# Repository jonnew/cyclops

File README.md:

## Cyclops LED Driver
Precision, wide-bandwidth current source with optional optical feedback mode
for driving high-power LEDs and laser diodes. Good for sneaking optogenetic
stimuli between fast things (e.g. galvo flyback on a 2P system). Good for
_really_ controlling the amount of light you deliver during 1P imaging or
optogenetic stimulation.

If you have questions or comments, please come talk on the [open-ephys discord server](https://discord.gg/H2pH4Cp8xb) 
in the #stimulation channel.

### Features
- Ultra-precise
- High power
- Up to 1.5A per LED
- Wide bandwidth
    - \~2.5 MHz -3 dB bandwidth
    - Maximum 100 ns 1.0A rise and fall times
- Current and optical feedback modes
- Built-in waveform generation
- Over-current protection
- Modular
    - Arduino compatible: internal waveform generation
    - Also, accepts external analog, gate, or trigger inputs

### Stimulus generation options
- External stimulus sequencer
- External digital trigger
    - TTL logic level
- External analog waveform generator
    - 0-5V analog signals
- Internal 12-bit DAC
    - Synchronized across up to 4 drivers
    - Arduino library
    - Programmable triggering logic
    - Respond to USB input

### Buying one
You can purchase a fully assembled cyclops driver from the [open-ephys
store](https://open-ephys.org/cyclops-led-driver). All profits go towards continued
operation of open-ephys.

### Documentation
Documentation and usage information are here: [MANUAL.pdf](./MANUAL.pdf). If you
have questions concerning usage, performance, etc., please direct them toward
the [Open Ephys forum](https://groups.google.com/forum/#!forum/open-ephys).

### Hardware Licensing
Copyright Jonathan P. Newman 2020.

This work is licensed under CC BY-NC-SA 4.0. To view a copy of this license,
visit https://creativecommons.org/licenses/by-nc-sa/4.0

__Note__: This license applies to hardware designs and documentation which reside
in the 'device', 'experimental', 'resources' folders of this repository along
with information in 'MANUAL.md' and 'MANUAL.pdf'

### Software Licensing
Copyright (c) Jonathan P. Newman 2017. All right reserved.

The code associated with the Cyclops project is free software: you can
redistribute it and/or modify it under the terms of the GNU General Public
License as published by the Free Software Foundation, either version 3 of the
License, or (at your option) any later version.

The code associated with the Cyclops project is distributed in the hope that it
will be useful, but WITHOUT ANY WARRANTY; without even the implied warranty of
MERCHANTABILITY or FITNESS FOR A PARTICULAR PURPOSE.  See the GNU General
Public License for more details.

You should have received a copy of the GNU General Public License along with
this code.  If not, see <http://www.gnu.org/licenses/>.

__Note__: This license applies to software/fireware source code which resides in in
the 'lib' folder of this repository

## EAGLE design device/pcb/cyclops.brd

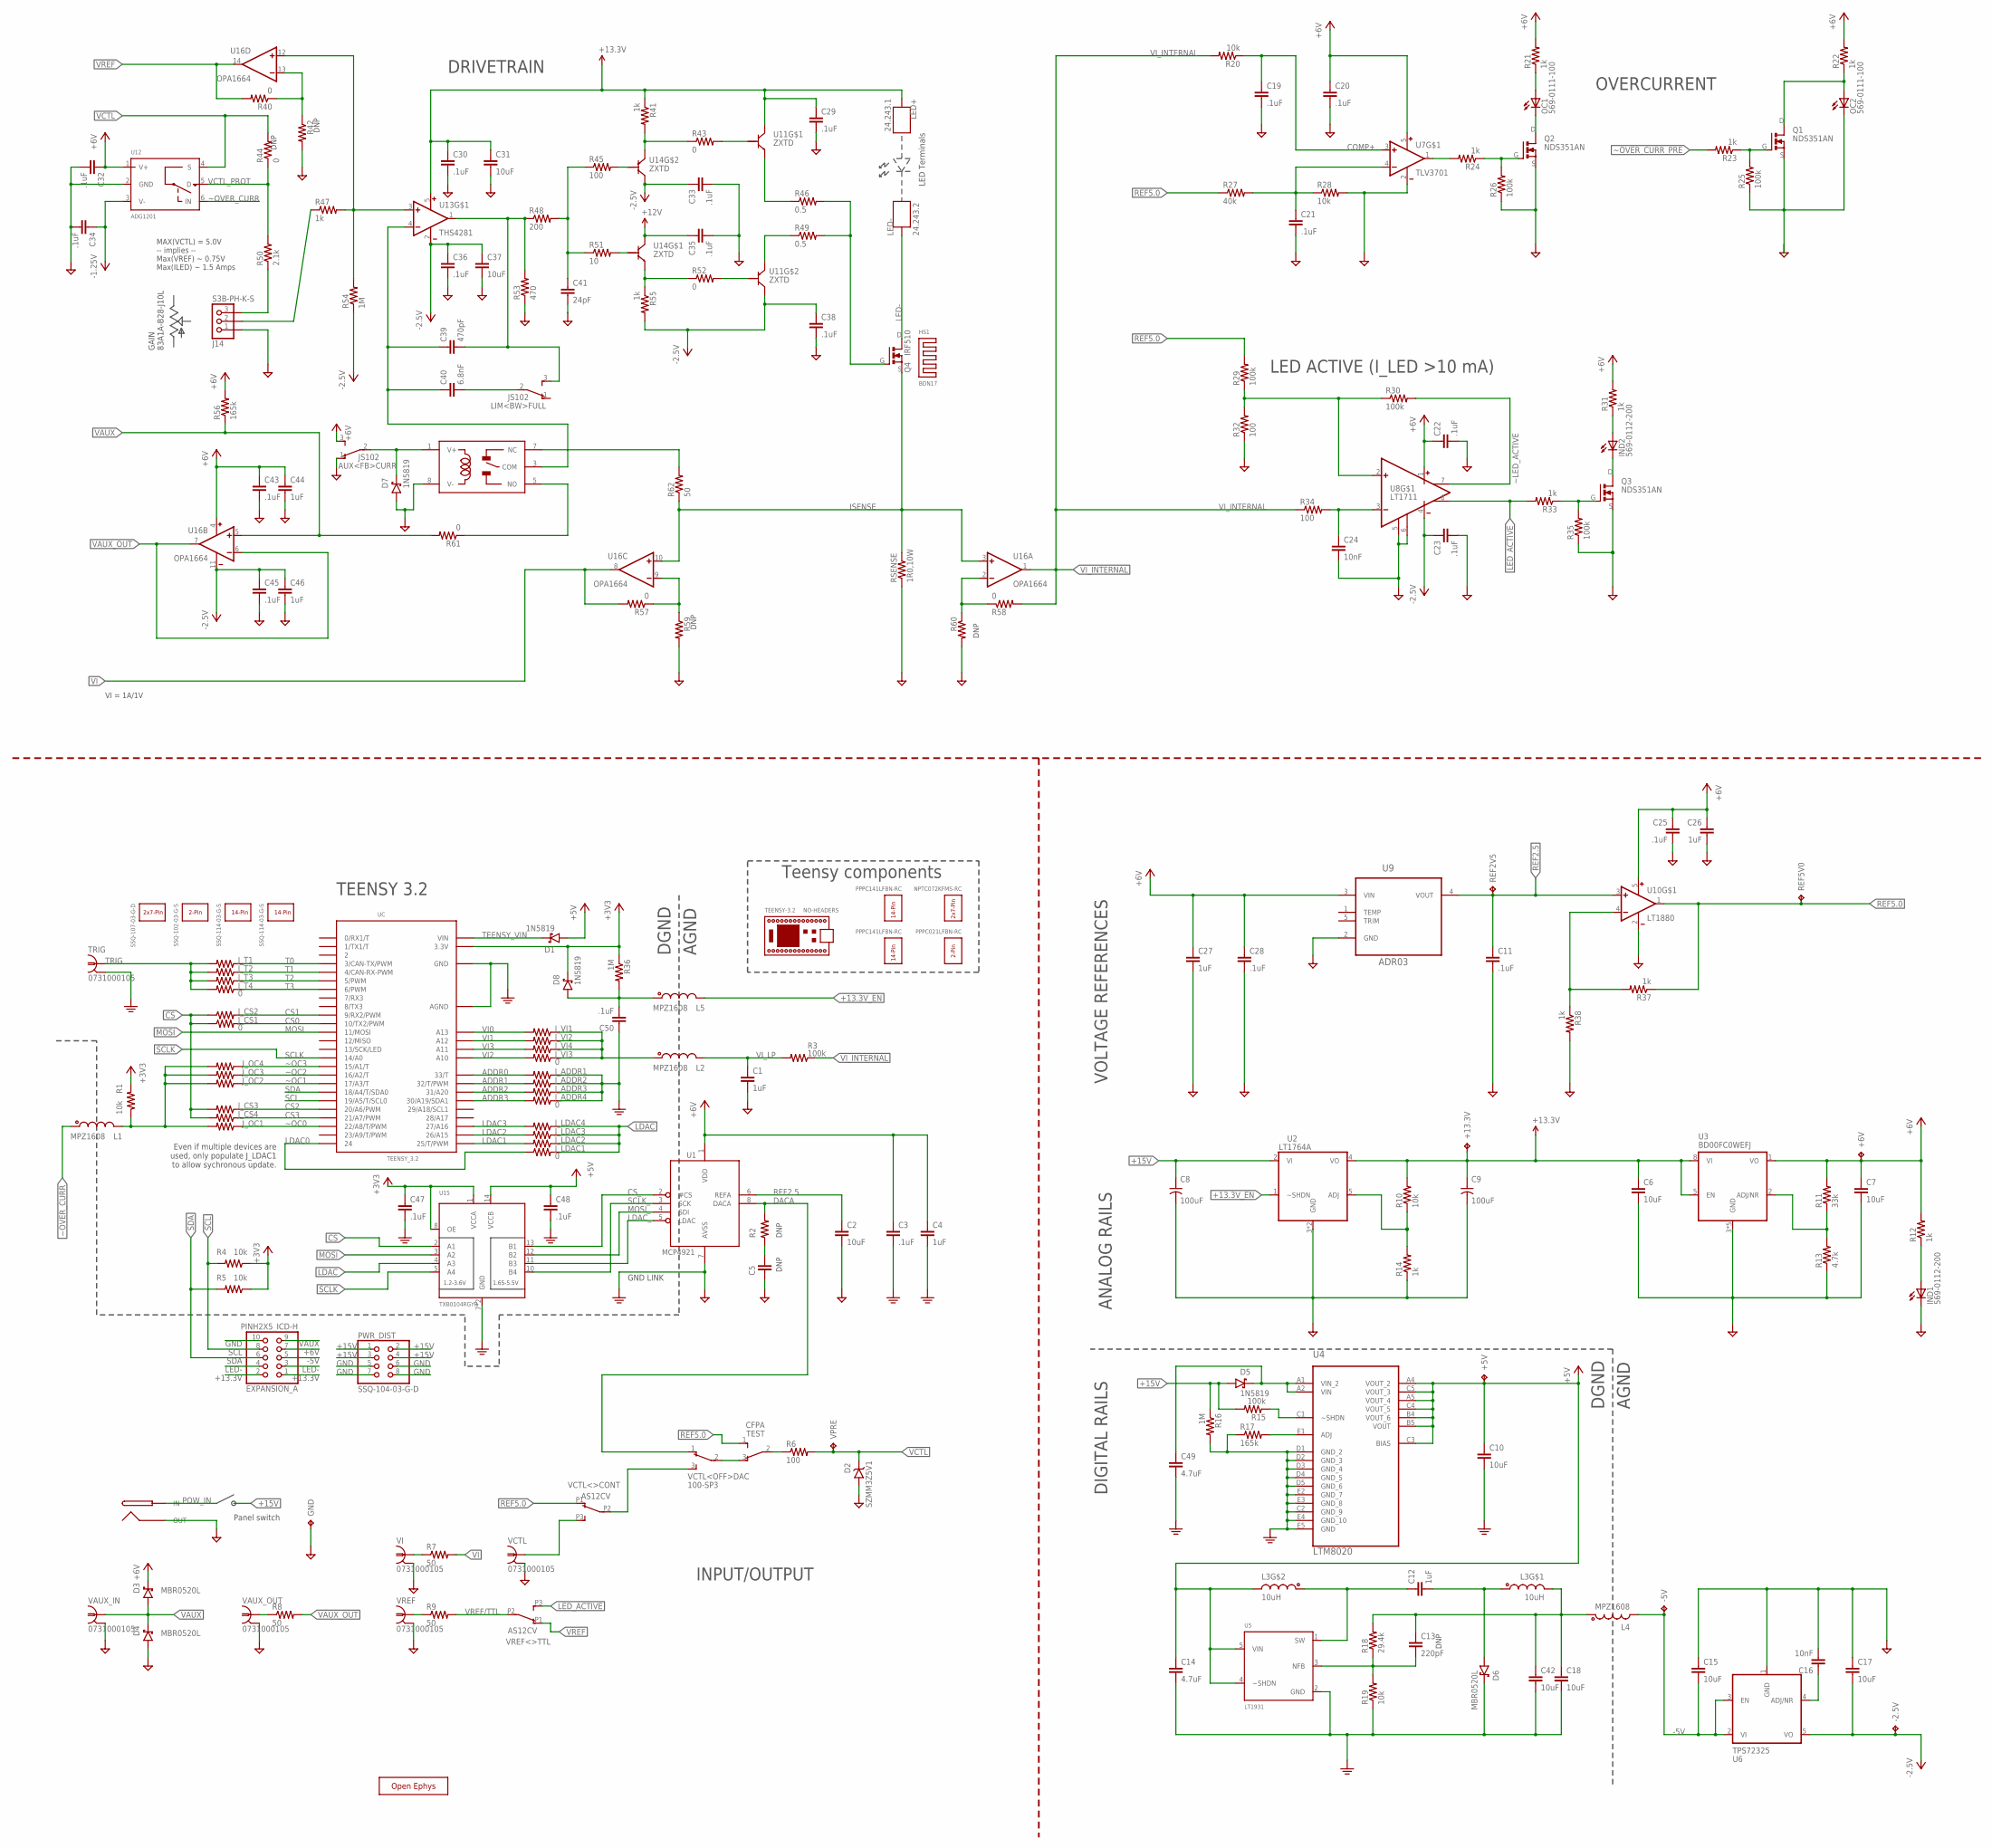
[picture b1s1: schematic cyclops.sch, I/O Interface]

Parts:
+5V, +6V, +13.3V: RCU-0C; RC0603
-2.5V, -5V: RCU-0C; RC0603
AUX<FB>CURR: JS102; JS102011SAQN
C1, C4, C12, C26, C27, C44, C46: 1uF; 0805
C2, C6, C7, C10, C15, C17, C18, C31, C37, C42: 10uF; 1206
C3, C11, C19, C20, C21, C22, C23, C25, C28, C29, C30, C32, C33, C34, C35, C36, C38, C43, C45, C47, C48, C50: .1uF; 0603
C5: C_0603; 0603
C8, C9: 100uF; 153CLV-0807
C13: 220pF; 0603
C14, C49: 4.7uF; 1206
C16, C24: 10nF; 0603
C39: 470pF; 0603
C40: 6.8nF; 0603
C41: 24pF; 0603
D1, D5, D7, D8: 1N5819; SOD123
D2: SZMM3Z5V1; SOD-323
D3, D4, D6: MBR0520L; SOD123
EXPANSION_A: PINH2X5_ICD-H; 2X05-IDC
GND: RCU-0C; RC0603
HS1: BDN17
IND: 569-0112-200; 569-011X-X00_LED_ARRAY
J14: S3B-PH-K-S
J_ADDR1, J_ADDR2, J_ADDR3, J_ADDR4: 0; 0402
J_CS1, J_CS2, J_CS3, J_CS4: 0; 0402
J_LDAC1, J_LDAC2, J_LDAC3, J_LDAC4: 0; 0402
J_OC1, J_OC2, J_OC3, J_OC4: 0; 0402
J_T1, J_T2, J_T3, J_T4: 0; 0402
J_VI1, J_VI2, J_VI3, J_VI4: 0; 0402
L1, L2, L4, L5: MPZ1608; 0603
L3: 10uH; CLS62
LED+: 24.243.1; A-2107
LED-: 24.243.2; A-2107
LIM<BW>FULL: JS102; JS102011SAQN
OC: 569-0111-100; 569-011X-X00_LED_ARRAY
POWER: PJ-063BH
PWR_DIST: SSQ-104-03-G-D; 2X04-BIG
Q1, Q2, Q3: NDS351AN; SOT23-GSD
Q4: IRF510; TO-262_01
R1, R4, R5, R10, R19, R20, R28: 10k; 0603
R2, R42, R59, R60: R_0603; 0603
R3, R15, R25, R26, R29, R30, R35: 100k; 0603
R6, R32, R34, R45: 100; 0603
R7, R8, R9, R62: 50; 1206
R11: 33k; 0603
R12, R14, R21, R22, R23, R24, R31, R33, R37, R38, R41, R47, R55: 1k; 0603
R13: 4.7k; 0603
R16, R36, R54: 1M; 0603
R17, R56: 165k; 0603
R18: 29.4k; 0603
R27: 40k; 0603
R40, R43, R44, R52, R57, R58, R61: 0; 0603
R46, R49: 0.5; 0603
R48: 200; 0603
R50: 2.1k; 0603
R51: 10; 0603
R53: 470; 0603
REF2V5, REF5V0: RCU-0C; RC0603
RSENSE: 1R0,10W; TO-252-THICK-FILM
S1: 1462042-8; 1462042
TEST: CFPA
TRIG: 0731000105
U1: MCP4921; SO08
U2: LT1764A; 5-DDPAK
U3: BD00FC0WEFJ; SOIC127P600X175-9N
U4: LTM8020; LGA21C127P5X5_625X625X242
U5: LT1931; SOT95P310X175-5N
U6: TPS72325; SOT-23-5
U7: TLV3701; SOT-23-5
U8: LT1711; SOP65P490X110-8N
U9: ADR03; SOT65P210X110-5N
U10: LT1880; SOT95P310X175-5N
U11, U14: ZXTD; SOT23-6
U12: ADG1201; SOT23-6
U13: THS4281; SOT95P310X175-5N
U15: TXB0104RGYR; 14QFN_2X6_2X2
U16: OPA1664; SO14
UC: TEENSY_3.2; TEENSY_3.1_CYCLOPS
VAUX_IN: 0731000105
VAUX_OUT: 0731000105
VCTL: 0731000105
VCTL<>CONT: AS12CV; AS12A*_SPDT
VCTL<OFF>DAC: 100-SP3; 2M1-SP1-T2-B4-M6RE
VI: 0731000105
VPRE: TPTP16R; RC0603
VREF: 0731000105
VREF<>TTL: AS12CV; AS12A*_SPDT
X1: OE-LOGO_14X10; OE-LOGO-14X10

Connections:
+3V3: C47.1, D8.C, R1.2, R4.1, R5.1, R36.1, U15.1 (VCCA), U15.8 (OE), UC.3.3V, UC.3.3V2 (3.3V)
+5V: +5V.1, C10.1, C14.1, C48.1, D1.A, L3.3 (2), U4.A4 (VOUT_2), U4.A5 (VOUT_4), U4.B4 (VOUT_6), U4.B5 (VOUT), U4.C3 (BIAS), U4.C4 (VOUT_5), U4.C5 (VOUT_3), U5.4 (~SHDN), U5.5 (VIN), U15.14 (VCCB)
+6V: +6V.1, AUX<FB>CURR.3, C3.1, C4.1, C7.1, C20.1, C22.1, C25.1, C26.1, C27.1, C28.1, C32.1, C43.1, C44.1, D3.C, EXPANSION_A.7, R11.2, R12.2, R21.2, R22.2, R31.2, R56.2, U1.1 (VDD), U3.1 (VO), U7.5 (V+), U8.1 (V+), U9.3 (VIN), U10.5 (V+), U12.1 (V+), U16.4 (V+)
+13.3V: +13.3V.1, C6.1, C9.+, C29.1, C30.1, C31.1, C35.1, EXPANSION_A.1, EXPANSION_A.2, LED+.1, LED+.2, R10.2, R41.1, U2.4 (VO), U3.5 (EN), U3.8 (VI), U11.1 (C), U13.5 (V+), U14.1 (C)
+13.3V_EN: L5.2, U2.1 (~SHDN)
+15V: C8.+, D5.A, PWR_DIST.1, PWR_DIST.2, PWR_DIST.3, PWR_DIST.4, R15.2, R16.1, U2.2 (VI)
-2.5V: -2.5V.1, C17.2, C23.1, C33.1, C34.1, C36.1, C37.1, C38.1, C45.1, C46.1, R54.1, R55.2, U6.5 (VO), U8.4 (V-), U11.3 (C), U12.3 (V-), U13.2 (V-), U14.3 (C), U16.11 (V-)
-5V: -5V.1, C15.2, EXPANSION_A.5, L4.2, U6.2 (VI), U6.3 (EN)
ADDR0: J_ADDR1.2, UC.33 (33/T)
ADDR1: J_ADDR2.2, UC.32 (32/T/PWM)
ADDR2: J_ADDR3.2, UC.31 (31/A20)
ADDR3: J_ADDR4.2, UC.30 (30/A19/SDA1)
COMP+: C19.1, R20.1, U7.3 (+IN)
CS: J_CS1.1, J_CS2.1, J_CS3.2, J_CS4.2, U15.2 (A1)
CS0: J_CS1.2, UC.10 (10/TX2/PWM)
CS1: J_CS2.2, UC.9 (9/RX2/PWM)
CS2: J_CS3.1, UC.20/A6 (20/A6/PWM)
CS3: J_CS4.1, UC.21/A7 (21/A7/PWM)
CS_: U1.2 (#CS), U15.13 (B1)
DACA: R2.2, U1.8 (DACA), VCTL<OFF>DAC.1
GND: AUX<FB>CURR.1, C1.2, C2.2, C3.2, C4.2, C5.2, C6.2, C7.2, C8.-, C9.-, C10.2, C11.2, C14.2, C15.1, C16.2, C17.1, C18.2, C19.2, C20.2, C21.2, C22.2, C23.2, C24.2, C25.2, C26.2, C27.2, C28.2, C29.2, C30.2, C31.2, C32.2, C33.2, C34.2, C35.2, C36.2, C37.2, C38.2, C41.2, C42.2, C43.2, C44.2, C45.2, C46.2, C47.2, C48.2, C49.2, C50.1, D2.A, D4.A, D6.C, D7.A, EXPANSION_A.10, GND.1, IND.C1 (C), J14.1, J_ADDR1.1, J_ADDR2.1, J_ADDR3.1, J_ADDR4.1, OC.C2 (C), POWER.2 (OUT), PWR_DIST.5, PWR_DIST.6, PWR_DIST.7, PWR_DIST.8, Q1.S, Q2.S, Q3.S, R13.1, R14.1, R16.2, R17.1, R19.1, R25.1, R26.1, R28.2, R32.1, R35.1, R38.2, R42.2, R53.1, R59.2, R60.2, RSENSE.1, S1.8 (V-), TRIG.2, TRIG.3 (2), U1.7 (AVSS), U2.3 (GND), U2.TAB (GND), U3.3 (GND), U3.4 (GND), U3.6 (GND), U3.7 (GND), U3.9 (GND), U4.C2 (GND_9), U4.D1 (GND_2), U4.D2 (GND_3), U4.D3 (GND_4), U4.D4 (GND_5), U4.D5 (GND_6), U4.E2 (GND_7), U4.E3 (GND_8), U4.E4 (GND_10), U4.E5 (GND), U5.2 (GND), U6.1 (GND), U7.2 (V-), U8.5 (LATCH), U8.6 (GND), U9.2 (GND), U10.2 (V-), U12.2 (GND), U15.7 (GND), U15.PAD (GND), UC.AGND, UC.GND, UC.GND2 (GND), VAUX_IN.2, VAUX_IN.3 (2), VAUX_OUT.2, VAUX_OUT.3 (2), VCTL.2, VCTL.3 (2), VI.2, VI.3 (2), VREF.2, VREF.3 (2)
IN: AUX<FB>CURR.2, D7.C, S1.1 (V+)
ISENSE: Q4.S, R62.1, RSENSE.2, U16.3 (+IN), U16.10 (+IN)
LDAC: J_LDAC1.2, J_LDAC2.1, J_LDAC3.1, J_LDAC4.1, U15.4 (A3)
LDAC0: J_LDAC1.1, UC.24
LDAC1: J_LDAC2.2, UC.25 (25/T/PWM)
LDAC2: J_LDAC3.2, UC.26 (26/A15)
LDAC3: J_LDAC4.2, UC.27 (27/A16)
LDAC_: U1.5 (LDAC), U15.11 (B3)
LED-: EXPANSION_A.3, EXPANSION_A.4, LED-.1, LED-.2, Q4.D
LED_ACTIVE: R33.2, U8.8 (~Q), VREF<>TTL.P3 (3)
MOSI: U15.3 (A2), UC.11 (11/MOSI)
MOSI_: U1.4 (SDI), U15.12 (B2)
unnamed: C5.1, R2.1
unnamed: OC.A1 (A), R21.1
unnamed: IND.A1 (A), R12.1
unnamed: R41.2, R43.1, U14.4 (E)
unnamed: C21.1, R27.2, R28.1, U7.4 (-IN)
unnamed: C50.2, D8.A, L5.1, R36.2
unnamed: C24.1, R34.2, U8.3 (-IN)
unnamed: R40.1, R42.1, U16.13 (-IN)
unnamed: OC.C1 (C), Q2.D
unnamed: R52.1, R55.1, U14.6 (E)
unnamed: R58.1, R60.1, U16.2 (-IN)
unnamed: R10.1, R14.2, U2.5 (ADJ)
unnamed: C39.2, LIM<BW>FULL.3, R48.1, R53.2, U13.1 (OUT)
unnamed: R6.1, TEST.2
unnamed: R57.1, R59.1, U16.9 (-IN)
unnamed: R37.2, R38.1, U10.4 (-IN)
unnamed: VCTL.1, VCTL<>CONT.P3 (3)
unnamed: C49.1, D5.C, U4.A1 (VIN_2), U4.A2 (VIN)
unnamed: R15.1, U4.C1 (~SHDN)
unnamed: R49.1, U11.4 (E)
unnamed: R46.1, U11.6 (E)
unnamed: Q4.G, R46.2, R49.2
unnamed: R24.2, U7.1 (OUT)
unnamed: Q2.G, R24.1, R26.2
unnamed: C12.1, L3.2 (1), U5.1 (SW)
unnamed: C12.2, D6.A, L3.1
unnamed: TEST.3 (1), VCTL<OFF>DAC.2
unnamed: C13.1, C18.1, C42.1, L3.4 (2), L4.1, R18.2
unnamed: C13.2, R18.1, R19.2, U5.3 (NFB)
unnamed: J14.2, R47.1
unnamed: R17.2, U4.E1 (ADJ)
unnamed: Q1.G, R23.1, R25.2
unnamed: C40.2, LIM<BW>FULL.2
unnamed: OC.A2 (A), Q1.D, R22.1
unnamed: R29.1, R30.1, R32.2, U8.2 (+IN)
unnamed: R11.1, R13.2, U3.2 (ADJ/NR)
unnamed: R52.2, U11.5 (B)
unnamed: R43.2, U11.2 (B)
unnamed: IND.A2 (A), R31.1
unnamed: IND.C2 (C), Q3.D
unnamed: R51.2, U14.2 (B)
unnamed: Q3.G, R33.1, R35.2
unnamed: R45.2, U14.5 (B)
unnamed: C16.1, U6.4 (ADJ/NR)
unnamed: R8.1, VAUX_OUT.1
unnamed: C39.1, C40.1, S1.3 (COM), U13.4 (-IN)
unnamed: R7.1, VI.1
unnamed: R9.1, VREF.1
unnamed: R62.2, S1.7 (NC)
unnamed: R61.1, S1.5 (NO)
unnamed: C41.1, R45.1, R48.2, R51.1
POW_IN: POWER.1 (IN)
REF2.5: C2.1, C11.1, REF2V5.1, U1.6 (REFA), U9.4 (VOUT), U10.3 (+IN)
REF5.0: R27.1, R29.2, R37.1, REF5V0.1, TEST.1 (3), U10.1 (OUT), VCTL<>CONT.P1 (1)
SCL: EXPANSION_A.8, R4.2, UC.19/A5 (19/A5/T/SCL0)
SCLK: U15.5 (A4), UC.14/A0
SCLK_: U1.3 (SCK), U15.10 (B4)
SDA: EXPANSION_A.6, R5.2, UC.18/A4 (18/A4/T/SDA0)
T0: J_T1.1, UC.3 (3/CAN-TX/PWM)
T1: J_T2.1, UC.4 (4/CAN-RX-PWM)
T2: J_T3.1, UC.5 (5/PWM)
T3: J_T4.1, UC.6 (6/PWM)
TEENSY_VIN: D1.C, UC.VIN
TRIG: J_T1.2, J_T2.2, J_T3.2, J_T4.2, TRIG.1
VAUX: D3.A, D4.C, EXPANSION_A.9, R56.1, R61.2, U16.5 (+IN), VAUX_IN.1
VAUX_OUT: R8.2, U16.6 (-IN), U16.7 (OUT)
VCTL: D2.C, R6.2, R44.2, U12.4 (S), VPRE.1
VCTL_PROT: R44.1, R50.2, U12.5 (D)
VCTL_PROTECT: J14.3, R50.1
VI: R7.2, R57.2, U16.8 (OUT)
VI0: J_VI1.2, UC.A13
VI1: J_VI2.2, UC.A12
VI2: J_VI3.2, UC.A10
VI3: J_VI4.2, UC.A11
VINPUT: VCTL<>CONT.P2 (2), VCTL<OFF>DAC.3
VI_IN: J_VI1.1, J_VI2.1, J_VI3.1, J_VI4.1, L2.1
VI_INTERNAL: R3.1, R20.2, R34.1, R58.2, U16.1 (OUT)
VI_LP: C1.1, L2.2, R3.2
VREF: R40.2, U16.14 (OUT), VREF<>TTL.P1 (1)
VREF/TTL: R9.2, VREF<>TTL.P2 (2)
_VREF: R47.2, R54.2, U13.3 (+IN), U16.12 (+IN)
~LED_ACTIVE: R30.2, U8.7 (Q)
~OC0: J_OC1.1, UC.22/A8 (22/A8/T/PWM)
~OC1: J_OC2.1, UC.17/A3 (17/A3/T)
~OC2: J_OC3.1, UC.16/A2 (16/A2/T)
~OC3: J_OC4.1, UC.15/A1 (15/A1/T)
~OVER_CURR: L1.1, U12.6 (IN)
~OVER_CURR_PRE: J_OC1.2, J_OC2.2, J_OC3.2, J_OC4.2, L1.2, R1.1, R23.2

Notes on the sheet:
GND LINK
INPUT/OUTPUT
Panel switch
AGND
DGND
Teensy components
DNP
Even if multiple devices are used, only populate J_LDAC1 to allow sychronous update.
ANALOG RAILS
DIGITAL RAILS
LED ACTIVE (I_LED >10 mA)
OVERCURRENT
VOLTAGE REFERENCES
LED Terminals
MAX(VCTL) = 5.0V -- implies -- Max(VREF) ~ 0.75V Max(ILED) ~ 1.5 Amps
VI = 1A/1V
DRIVETRAIN
GAIN 83A1A-B28-J10L
TEENSY 3.2

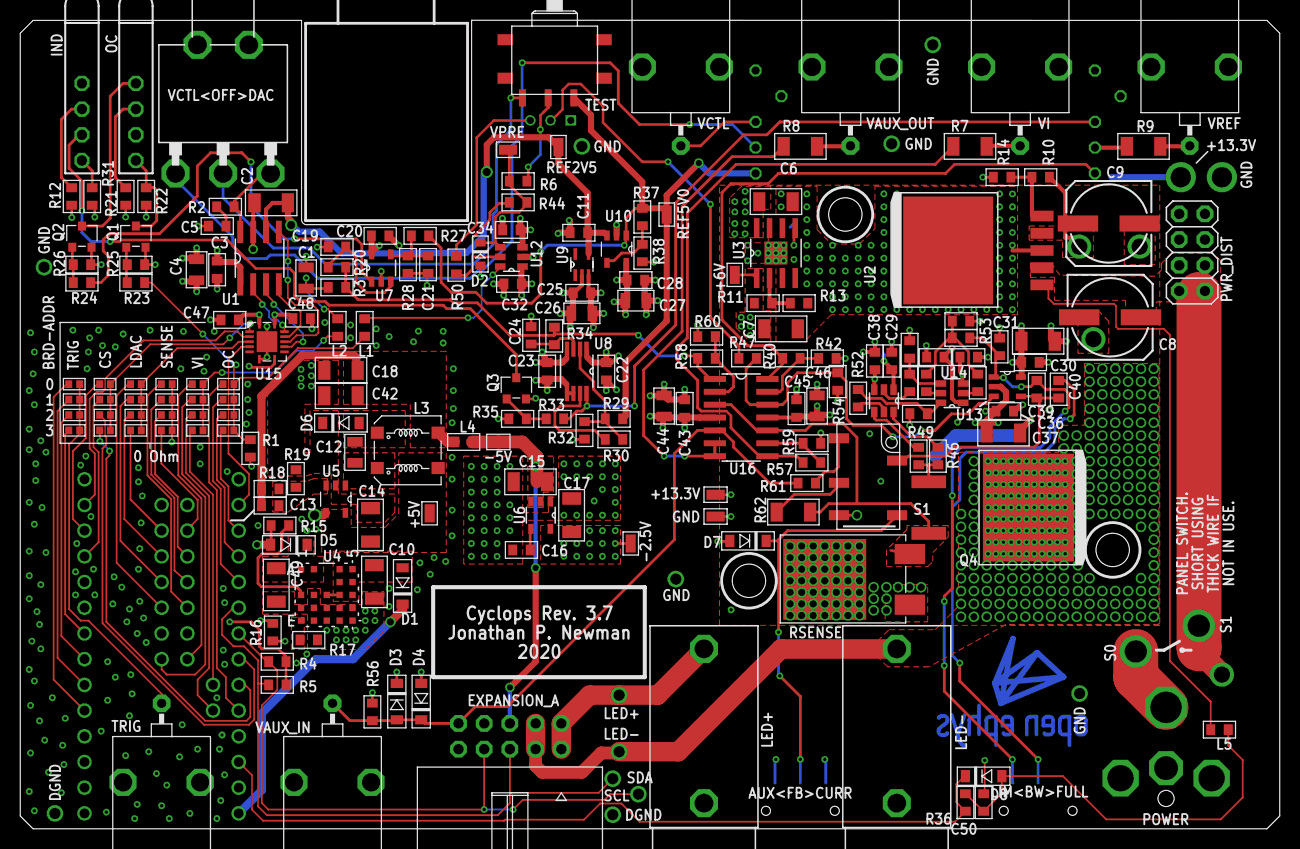
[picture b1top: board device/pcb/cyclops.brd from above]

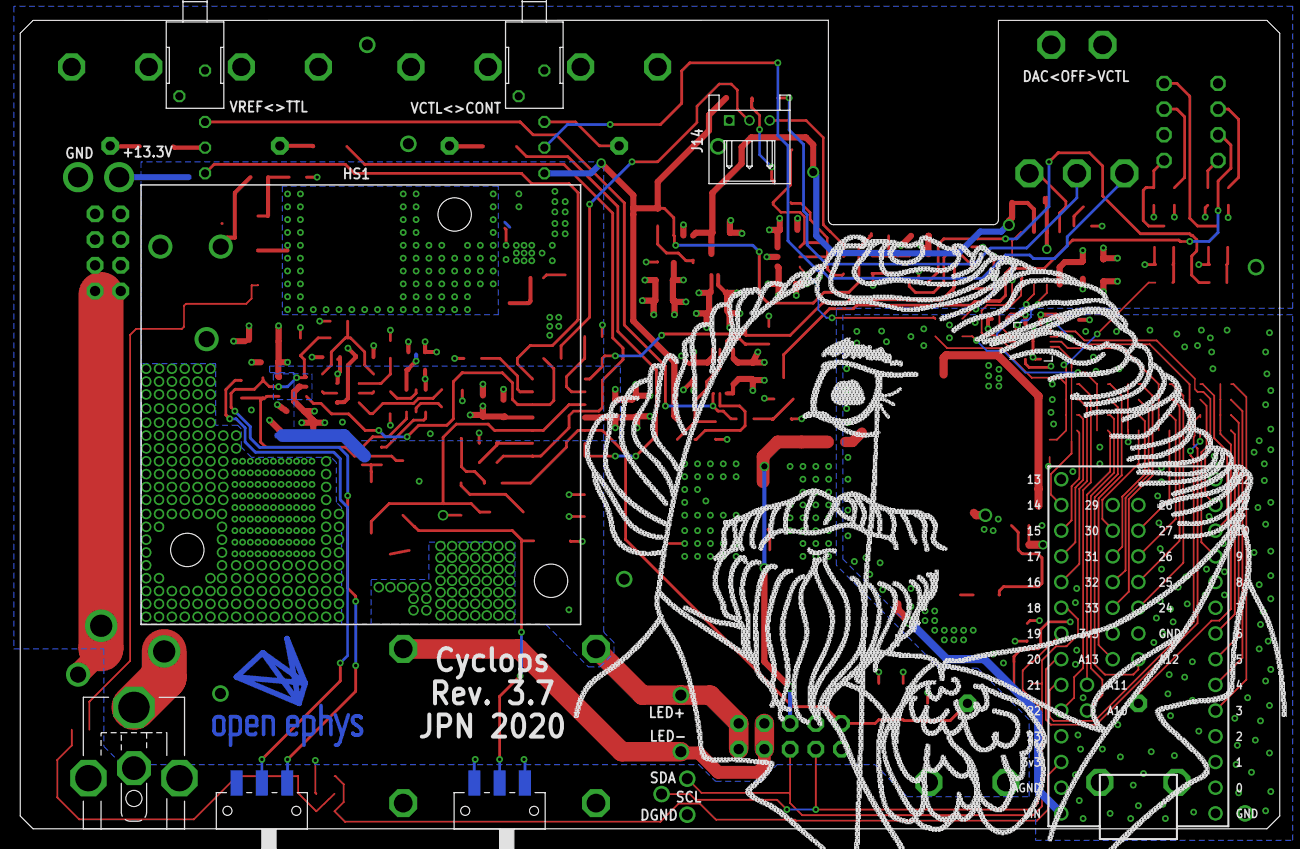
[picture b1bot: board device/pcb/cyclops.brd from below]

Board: 4 copper layers, 124.5 x 79.9 mm, 203 parts (10 on the bottom side), 120 nets.

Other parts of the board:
U$56: CYCLOPS_LOGO

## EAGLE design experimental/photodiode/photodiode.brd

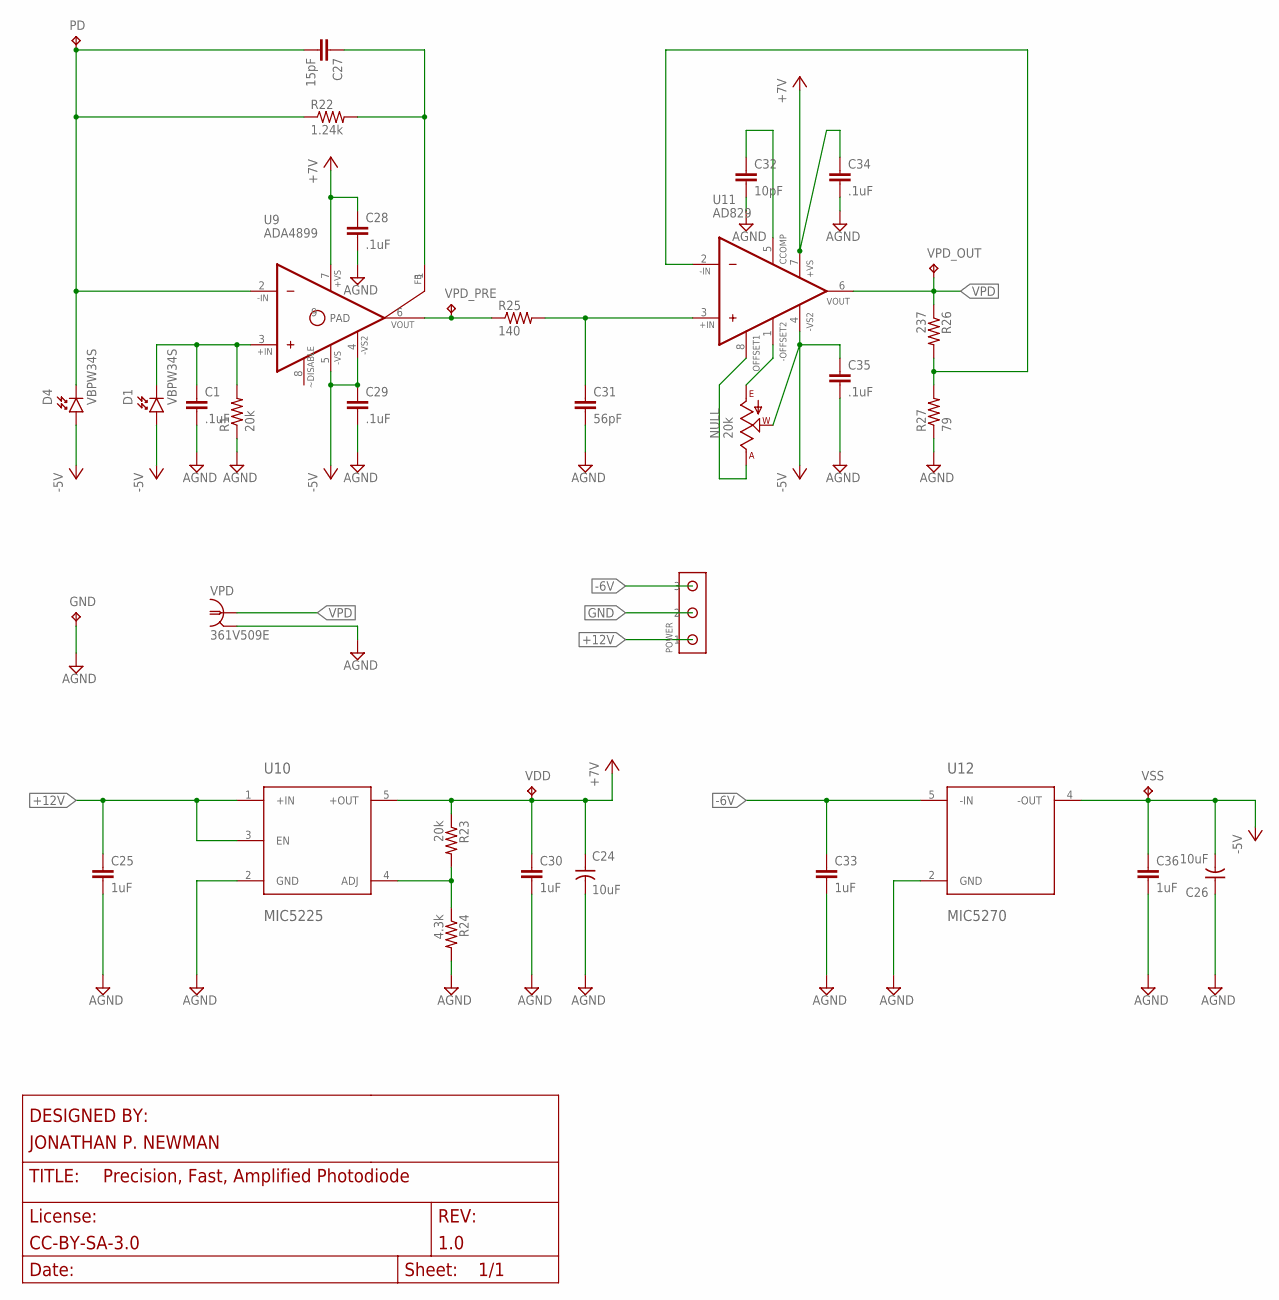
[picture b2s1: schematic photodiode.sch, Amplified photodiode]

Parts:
C1, C28, C29, C34, C35: .1uF; 0603
C24, C26: 10uF; 6032M-POL
C25, C30, C33, C36: 1uF; 0805
C27: 15pF; 0603
C31: 56pF; 0603
C32: 10pF; 0603
D1, D4: VBPW34S
GND: TPTP08R; TP08R
NULL: 20k; SM-42/43A
PD: TPTP08R; TP08R
POWER: S2B-PH-K-S; SCREW3
R1, R23: 20k; 0603
R22: 1.24k; 0603
R24: 4.3k; 0603
R25: 140; 0603
R26: 237; 0603
R27: 79; 0603
U9: ADA4899; SOIC127P600X175-9N
U10: MIC5225; SOT-23-5
U11: AD829; SOIC127P600X175-8N
U12: MIC5270; SOT-23-5
VDD: TPTP08R; TP08R
VPD: 361V509E
VPD_OUT: TPTP08R; TP08R
VPD_PRE: TPTP08R; TP08R
VSS: TPTP08R; TP08R

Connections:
+7V: C24.+, C28.1, C30.1, C34.1, R23.1, U9.7 (+VS), U10.5 (+OUT), U11.7 (+VS), VDD.TP
+12V: C25.1, POWER.P$1 (1), U10.1 (+IN), U10.3 (EN)
-5V: C26.-, C29.1, C35.1, C36.1, D1.A, D4.A, NULL.2 (W), U9.4 (-VS_2), U9.5 (-VS), U11.4 (-VS), U12.4 (-OUT), VSS.TP
-6V: C33.1, POWER.P$3 (3), U12.5 (-IN)
GND: C1.2, C24.-, C25.2, C26.+, C28.2, C29.2, C30.2, C31.2, C32.2, C33.2, C34.2, C35.2, C36.2, GND.TP, POWER.P$2 (2), R1.1, R24.2, R27.1, U10.2 (GND), U12.2 (GND), VPD.2, VPD.3 (2)
unnamed: C1.1, D1.C, R1.2, U9.3 (+IN)
unnamed: C27.1, R22.2, U9.1 (FEEDBACK)
unnamed: C27.2, D4.C, PD.TP, R22.1, U9.2 (-IN)
unnamed: NULL.3 (E), U11.1 (OFS_2)
unnamed: R25.1, U9.6 (VOUT), VPD_PRE.TP
unnamed: R23.2, R24.1, U10.4 (ADJ)
unnamed: R26.2, R27.2, U11.2 (-IN)
unnamed: NULL.1 (A), U11.8 (OFS)
unnamed: C32.1, U11.5 (CCOMP)
VPD: R26.1, U11.6 (OUTPUT), VPD.1, VPD_OUT.TP
VPD_PRE: C31.1, R25.2, U11.3 (+IN)

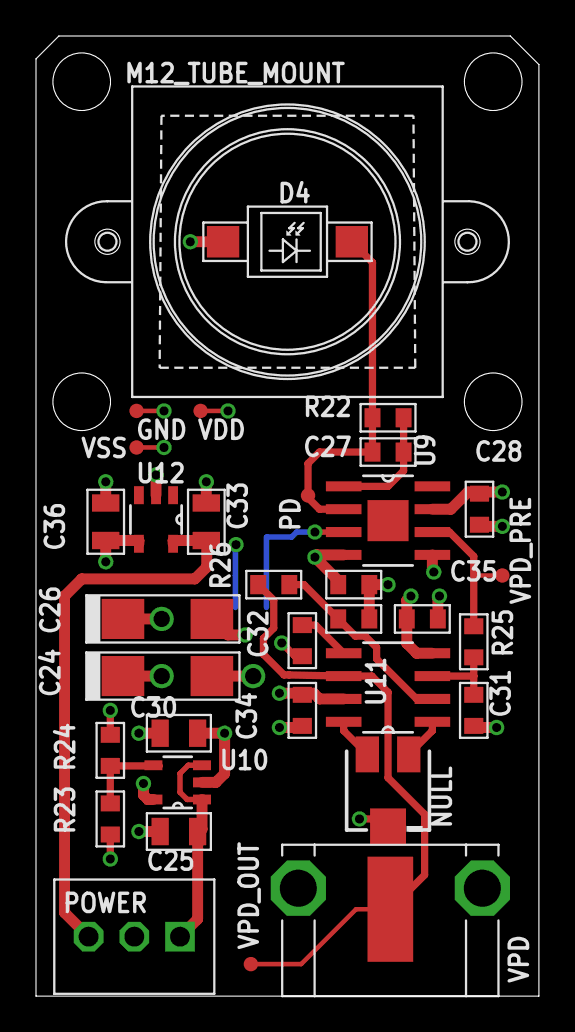
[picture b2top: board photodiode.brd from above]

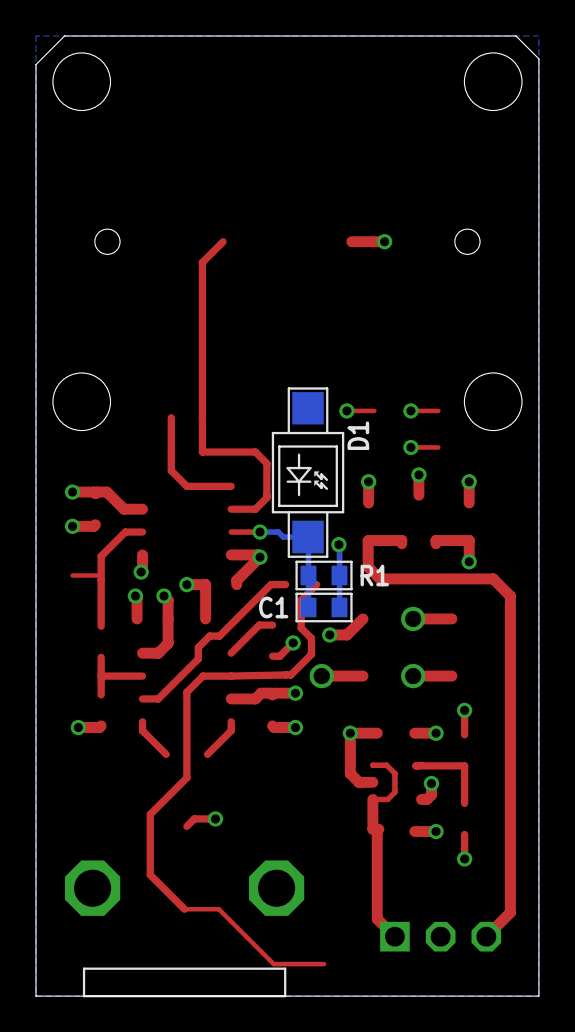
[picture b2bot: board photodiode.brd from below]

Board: 4 copper layers, 27.9 x 53.3 mm, 37 parts (3 on the bottom side), 16 nets.

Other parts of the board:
M12_TUBE_MOUNT: PT-LH001

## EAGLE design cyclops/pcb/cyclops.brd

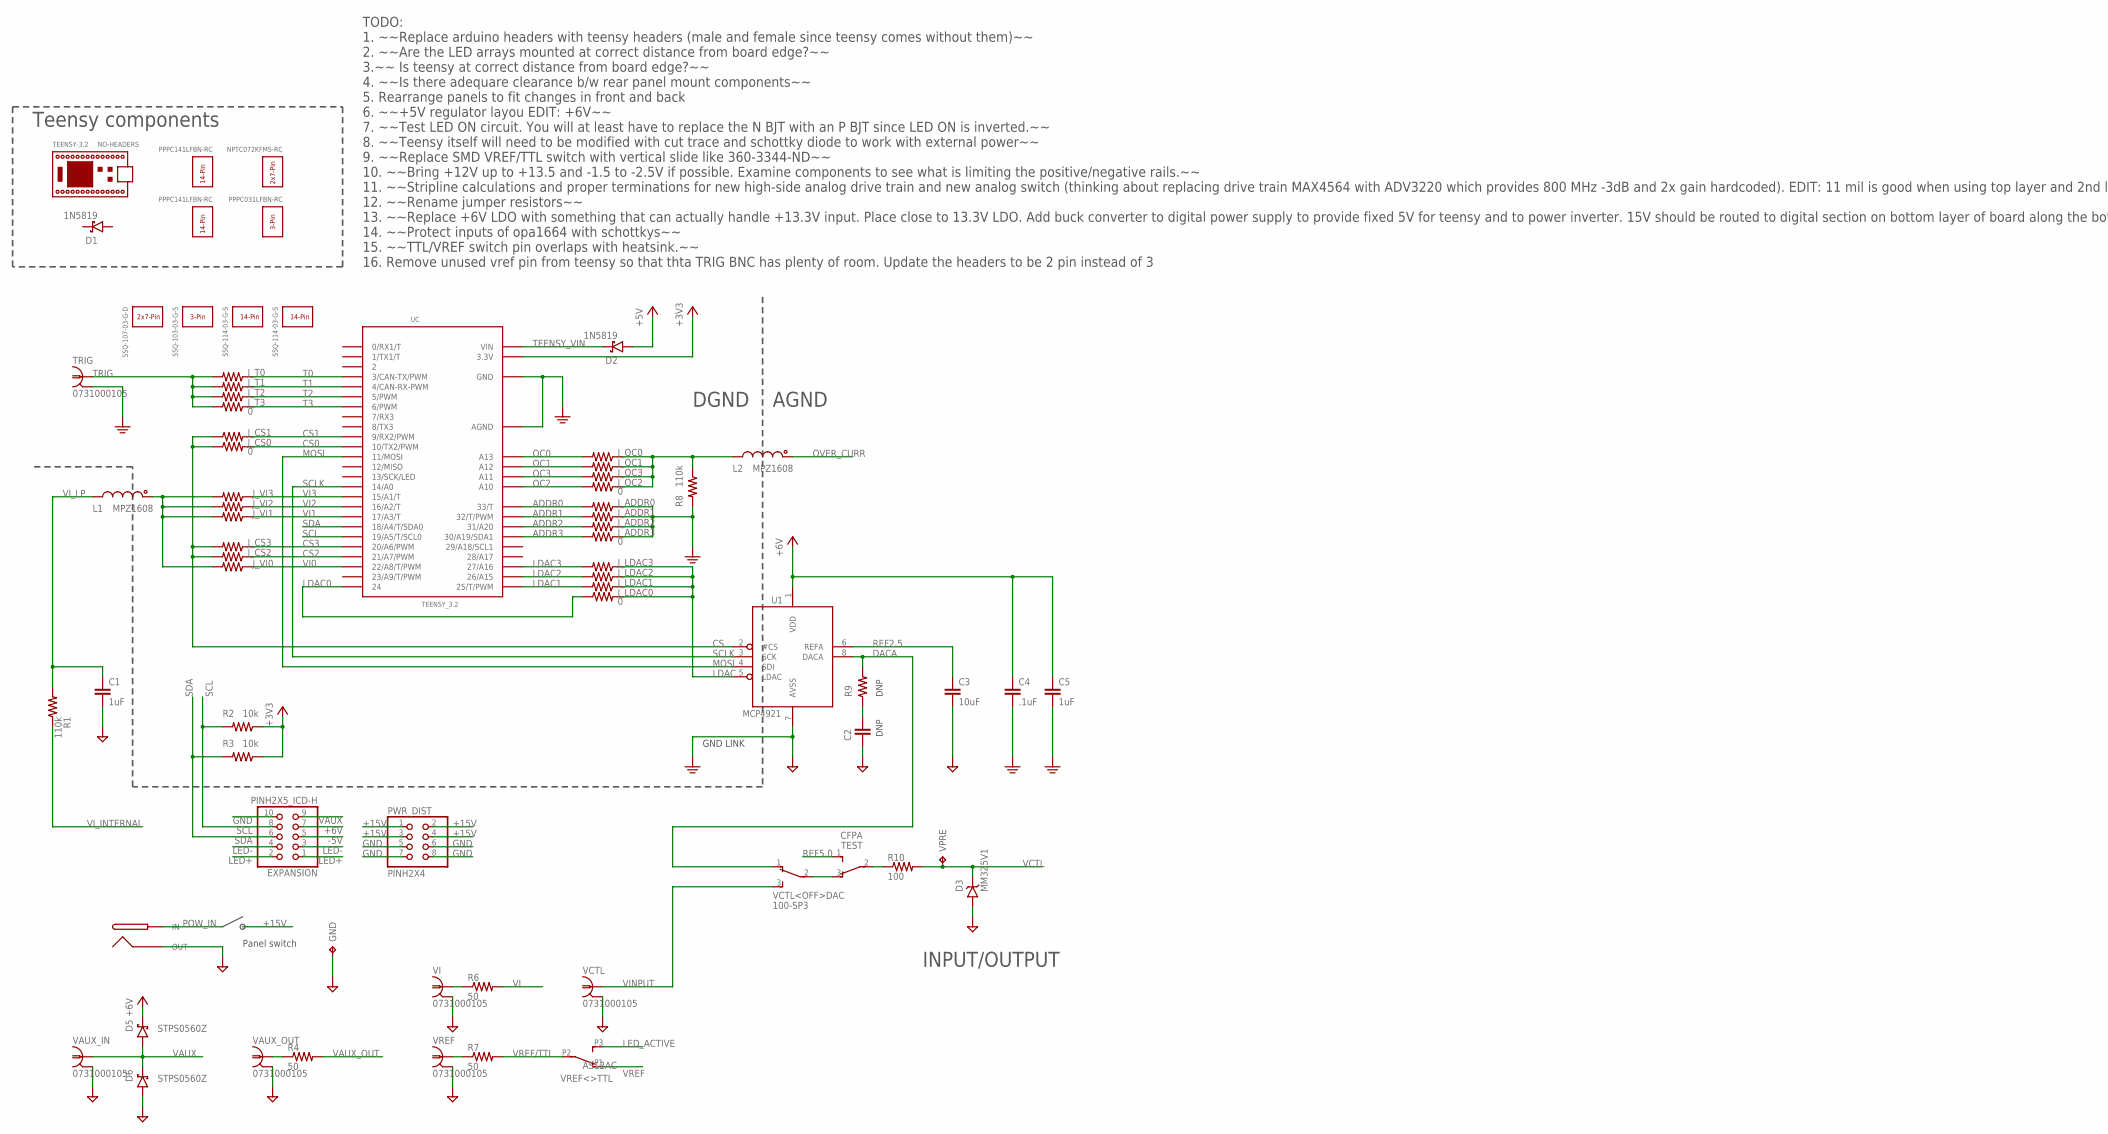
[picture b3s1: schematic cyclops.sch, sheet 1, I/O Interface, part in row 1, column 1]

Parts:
C1, C5: 1uF; 0805
C2: C_0603; 0603
C3: 10uF; 1206
C4: .1uF; 0603
D1, D2: 1N5819; SOD123
D3: MM3Z5V1; SOD-323
D5, D6: STPS0560Z; SOD123
EXPANSION: PINH2X5_ICD-H; 2X05-IDC
GND: RCU-0C; RC0603
J_ADDR0, J_ADDR1, J_ADDR2, J_ADDR3: 0; 0402
J_CS0, J_CS1, J_CS2, J_CS3: 0; 0402
J_LDAC0, J_LDAC1, J_LDAC2, J_LDAC3: 0; 0402
J_OC0, J_OC1, J_OC2, J_OC3: 0; 0402
J_T0, J_T1, J_T2, J_T3: 0; 0402
J_VI0, J_VI1, J_VI2, J_VI3: 0; 0402
L1, L2: MPZ1608; 0603
POWER: PJ-063BH
PWR_DIST: PINH2X4; 2X04-BIG
R1, R8: 110k; 0603
R2, R3: 10k; 0603
R4, R6, R7: 50; 1206
R9: R_0603; 0603
R10: 100; 0603
TEST: CFPA
TRIG: 0731000105
U1: MCP4921; SO08
UC: TEENSY_3.2; TEENSY_3.1_CYCLOPS
VAUX_IN: 0731000105
VAUX_OUT: 0731000105
VCTL: 0731000105
VCTL<OFF>DAC: 100-SP3; 2M1-SP1-T2-B4-M6RE
VI: 0731000105
VPRE: TPTP16R; RC0603
VREF: 0731000105
VREF<>TTL: AS12AC; AS12A*_SPDT

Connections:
+3V3: R2.1, R3.1, UC.3.3V, UC.3.3V2 (3.3V)
+5V: D2.A; also elsewhere on the board
+6V: C4.1, C5.1, D5.C, EXPANSION.7, U1.1 (VDD); also elsewhere on the board
+15V: PWR_DIST.1, PWR_DIST.2, PWR_DIST.3, PWR_DIST.4; also elsewhere on the board
-5V: EXPANSION.5; also elsewhere on the board
ADDR0: J_ADDR0.2, UC.33 (33/T)
ADDR1: J_ADDR1.2, UC.32 (32/T/PWM)
ADDR2: J_ADDR2.2, UC.31 (31/A20)
ADDR3: J_ADDR3.2, UC.30 (30/A19/SDA1)
CS: J_CS0.1, J_CS1.1, J_CS2.2, J_CS3.2, U1.2 (#CS)
CS0: J_CS0.2, UC.10 (10/TX2/PWM)
CS1: J_CS1.2, UC.9 (9/RX2/PWM)
CS2: J_CS2.1, UC.21/A7 (21/A7/PWM)
CS3: J_CS3.1, UC.20/A6 (20/A6/PWM)
DACA: R9.2, U1.8 (DACA), VCTL<OFF>DAC.1
GND: C1.2, C2.2, C3.2, C4.2, C5.2, D3.A, D6.A, EXPANSION.10, GND.1, J_ADDR0.1, J_ADDR1.1, J_ADDR2.1, J_ADDR3.1, POWER.2 (OUT), PWR_DIST.5, PWR_DIST.6, PWR_DIST.7, PWR_DIST.8, R8.2, TRIG.2, TRIG.3 (2), U1.7 (AVSS), UC.AGND, UC.GND, UC.GND2 (GND), VAUX_IN.2, VAUX_IN.3 (2), VAUX_OUT.2, VAUX_OUT.3 (2), VCTL.2, VCTL.3 (2), VI.2, VI.3 (2), VREF.2, VREF.3 (2); also elsewhere on the board
LDAC: J_LDAC0.2, J_LDAC1.1, J_LDAC2.1, J_LDAC3.1, U1.5 (LDAC)
LDAC0: J_LDAC0.1, UC.24
LDAC1: J_LDAC1.2, UC.25 (25/T/PWM)
LDAC2: J_LDAC2.2, UC.26 (26/A15)
LDAC3: J_LDAC3.2, UC.27 (27/A16)
LED+: EXPANSION.1, EXPANSION.2; also elsewhere on the board
LED-: EXPANSION.3, EXPANSION.4; also elsewhere on the board
LED_ACTIVE: VREF<>TTL.P3 (3); also elsewhere on the board
MOSI: U1.4 (SDI), UC.11 (11/MOSI)
unnamed: C2.1, R9.1
unnamed: R10.1, TEST.2
unnamed: TEST.3 (1), VCTL<OFF>DAC.2
unnamed: R4.1, VAUX_OUT.1
unnamed: R6.1, VI.1
unnamed: R7.1, VREF.1
unnamed: J_VI0.2, J_VI1.2, J_VI2.2, J_VI3.2, L1.1
OC0: J_OC0.2, UC.A13
OC1: J_OC1.2, UC.A12
OC2: J_OC2.2, UC.A10
OC3: J_OC3.2, UC.A11
OVER_CURR: L2.1; also elsewhere on the board
OVER_CURR_PRE: J_OC0.1, J_OC1.1, J_OC2.1, J_OC3.1, L2.2, R8.1; also elsewhere on the board
POW_IN: POWER.1 (IN)
REF2.5: C3.1, U1.6 (REFA); also elsewhere on the board
REF5.0: TEST.1 (3); also elsewhere on the board
SCL: EXPANSION.8, R2.2, UC.19/A5 (19/A5/T/SCL0)
SCLK: U1.3 (SCK), UC.14/A0
SDA: EXPANSION.6, R3.2, UC.18/A4 (18/A4/T/SDA0)
T0: J_T0.1, UC.3 (3/CAN-TX/PWM)
T1: J_T1.1, UC.4 (4/CAN-RX-PWM)
T2: J_T2.1, UC.5 (5/PWM)
T3: J_T3.1, UC.6 (6/PWM)
TEENSY_VIN: D2.C, UC.VIN
TRIG: J_T0.2, J_T1.2, J_T2.2, J_T3.2, TRIG.1
VAUX: D5.A, D6.C, EXPANSION.9, VAUX_IN.1; also elsewhere on the board
VAUX_OUT: R4.2; also elsewhere on the board
VCTL: D3.C, R10.2, VPRE.1; also elsewhere on the board
VI: R6.2; also elsewhere on the board
VI0: J_VI0.1, UC.22/A8 (22/A8/T/PWM)
VI1: J_VI1.1, UC.17/A3 (17/A3/T)
VI2: J_VI2.1, UC.16/A2 (16/A2/T)
VI3: J_VI3.1, UC.15/A1 (15/A1/T)
VINPUT: VCTL.1, VCTL<OFF>DAC.3
VI_INTERNAL: R1.1; also elsewhere on the board
VI_LP: C1.1, L1.2, R1.2
VREF: VREF<>TTL.P1 (1); also elsewhere on the board
VREF/TTL: R7.2, VREF<>TTL.P2 (2)

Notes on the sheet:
GND LINK
INPUT/OUTPUT
Panel switch
AGND
DGND
TODO: 1. ~~Replace arduino headers with teensy headers (male and female since teensy comes without them)~~ 2. ~~Are the LED arrays mounted at correct distance from board edge?~~ 3.~~ Is teensy at correct distance from board edge?~~ 4. ~~Is there adequare clearance b/w rear panel mount components~~ 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
Teensy components
DNP

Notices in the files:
cyclops/cyclops_r3.brd:
CC BY-SA-NC 4.0
experimental/photodiode/photodiode.sch:
LICENSE: CC-BY-SA-3.0
pcb/cyclops_r3/cyclops_r3p1.brd:
License: CC BY-SA 4.0
parts and their libraries:
SparkFun-Aesthetics: Licensing: Creative Commons ShareAlike 4.0 International - https://creativecommons.org/licenses/by-sa/4.0
